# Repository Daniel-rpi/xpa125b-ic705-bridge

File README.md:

# IC-705 ↔ Xiegu XPA125B via TTGO Bluetooth-Bridge

Ein LilyGO **TTGO T-Display v1.1** (ESP32) verbindet sich per **Bluetooth
Classic (CI-V-over-SPP)** mit einem Icom **IC-705** und steuert darüber eine
nachgeschaltete Xiegu **XPA125B**-Endstufe (100 W HF-Verstärker) vollautomatisch:
Bandumschaltung, PTT und – seit Kurzem – eine softwareseitige ALC-basierte
Schutzschaltung, die eingreift, bevor die PA in ihre eigene harte
Fehlerabschaltung läuft.

Kein Kabelsalat zwischen 705 und PA, kein manuelles Bandwechseln an der PA, und
eine grobe, aber wirksame Warnstufe vor Übersteuerung – bei einem Funkgerät, das
selbst gar keine passende ACC-Buchse für so eine PA hat.

*(English: An ESP32 board bridges an Icom IC-705 (Bluetooth CI-V) to a Xiegu
XPA125B HF amplifier — automatic band switching, PTT, and a software ALC-based
overdrive protection layer. See [docs/alc-protection.md](docs/alc-protection.md)
for a full English write-up of the protection logic.)*

## ⚠️ Sicherheitshinweise (bitte vor dem Nachbau lesen)

- **≥ 3,2 V am PTT-Eingang der XPA125B zerstört deren internen Prozessor
  dauerhaft** (laut offiziellem Handbuch). Der PTT-Ausgang des TTGO läuft daher
  ausschließlich über eine galvanische Trennung (Optokoppler bzw. MOSFET-gegen-GND,
  siehe unten) – niemals GPIO26 direkt an die PA anschließen.
- Diese Firmware sendet zur reinen Anzeige (Frequenz/Modus/TX-Status/Uhrzeit)
  **ausschließlich CI-V-Lesebefehle**. Echte Sende-Kommandos (Leistung setzen,
  Modus setzen, PTT) gibt es nur in der Tune-Sequenz (Taster) und der
  ALC-Schutzfunktion – beide sind im Quellcode ausführlich kommentiert.
- Alle hier beschriebenen Werte (Bandspannungen, PTT-Pegel, ALC-Schwellen) sind
  **an einem konkreten IC-705 und einer konkreten XPA125B gemessen**. Vor dem
  Anschließen an eigene Hardware selbst nachmessen, nicht blind übernehmen.
- Kein Ersatz für die Schutzabschaltung der PA selbst – nur eine zusätzliche,
  frühere Warnstufe.
- Nachbau/Nutzung auf eigene Verantwortung.

## Basiert auf / Danke an

Dieses Projekt wäre ohne die Vorarbeit von **DL1BZ** nicht in dieser Form
entstanden:

- [dl1bz/ESP32-IC705BT-PA](https://github.com/dl1bz/ESP32-IC705BT-PA) – das
  ursprüngliche Konzept (ESP32 + Bluetooth-CI-V + Optokoppler-PTT + PWM/RC-Band-
  spannung für eine XPA125B), inklusive Forks von
  [PE1OFO](https://github.com/PE1OFO/IC-705-BlueTooth-Controller) und
  [DK8HC](https://github.com/dk8hc/IC-705-BlueTooth-Controller).

**Wichtig, damit klar ist, was wovon abstammt:** Die hier veröffentlichte
Firmware ist ein **komplett eigenständig geschriebener Sketch** (kein Codeauszug
aus den obigen Repos, keine `CIVmasterLib`-Abhängigkeit) – die Übernahme betrifft
das **Konzept und einzelne kalibrierte Werte**: die Verdrahtung
GPIO26→PTT/GPIO27→Bandspannung, die Bandspannungstabelle aus dem Xiegu-Handbuch
und die daraus abgeleitete Lastkorrektur (`corrMv` in `firmware/bands.h`) sind
1:1 aus `z_userprog.ino` von DL1BZ übernommen. Alles Weitere (TFT-Anzeige,
Uhrzeit/UTC, Tune-Sequenz mit FB/NG-Bestätigung, ALC-Auslesung samt
Schutzschaltung, das komplette PMR-171-BLE-Modul, die Daughterboard-Platine) ist
eigene Arbeit dieses Projekts.

## Fotos

| Rückseite (fertiges Modul) | Draufsicht (fertiges Modul) | Innenansicht |
|---|---|---|
|  |  |  |

## Hardware

### Übersicht

```
IC-705 ──(Bluetooth Classic, CI-V-over-SPP)──> TTGO T-Display v1.1 (ESP32)
                                                     │  GPIO26 (PTT, über Opto/MOSFET gegen GND)
                                                     │  GPIO27 (PWM → RC 470Ω/22µF → Bandspannung)
                                                     │  GPIO36 (ADC, über 220Ω ← ALC-Ausgang, Pin 4)
                                                     ▼
                                        Xiegu XPA125B – ACC-Buchse (6-pol. Mini-DIN)
                                        Pin 1 = +12…14,5V (Versorgung der Platine) ⚠️ siehe unten
                                        Pin 2 = PTT (≥3,2V = Prozessorschaden!)
                                        Pin 3 = Bandspannung
                                        Pin 4 = ALC-Ausgang (~1–4V, invertiert)
                                        Pin 6 = GND
```

> **⚠️ ACC-Pin 1 ist im offiziellen Xiegu-Handbuch als N/C (nicht belegt)
> dokumentiert – liegt bei unserem (unmodifizierten, werksseitigen) Exemplar
> aber real die volle Versorgungsspannung der PA an** (gemessen ~12,85 V bei
> eingeschalteter PA am Netzteil, skaliert entsprechend mit der extern
> angelegten 12–14,5 V-Spannung). Genau das macht die eigene Stromversorgung
> des TTGO über die ACC-Buchse erst möglich, ohne ein zweites Netzteil oder
> einen Eingriff in die PA. Diese Diskrepanz zwischen Handbuch und Realität hat
> uns selbst lange beschäftigt (mehrere Diskussionsrunden, bis wir es am Ende
> direkt mit dem Multimeter durchgemessen haben) – **vor dem Nachbau unbedingt
> selbst am eigenen Gerät nachmessen**, statt sich auf das Handbuch *oder*
> diese Notiz zu verlassen. Xiegu könnte diese Pinbelegung in einer anderen
> Fertigungscharge/Hardwarerevision jederzeit ändern, ohne das zu
> dokumentieren – schließlich war sie nie offiziell zugesichert.

Das TTGO bezieht seine eigene 3,3-V-Versorgung direkt aus dieser
(inoffiziellen, aber real anliegenden) ACC-Pin-1-Spannung der PA (isolierter
DC/DC-Wandler bzw. Buck-Regler auf dem Daughterboard, siehe `hardware/`) –
**kein separates USB-Netzteil nötig, aber USB und PA-Strom dürfen nicht
gleichzeitig anliegen** (kein Akku auf der Platine, zwei Spannungsquellen
würden sich gegenseitig stören).

### Eigene SMD-Platine (Daughterboard)

Statt der Verkabelung frei fliegend aufzubauen: ein fertig geroutetes,
2-lagiges Daughterboard, das exakt auf die Stiftleisten des TTGO T-Display v1.1
gesteckt wird (Pin-Raster 1:1 aus der offiziellen LilyGO-Eagle-Bibliothek
übernommen), inkl. isoliertem Step-Down-Wandler, PTT-Schaltung und
RC-Filter für die Bandspannung.

- **[hardware/DESIGN.md](hardware/DESIGN.md)** – vollständige Bauteilliste,
  Netzliste, Layout-Vorgaben, Inbetriebnahme-Checkliste
- **[hardware/BESTELLUNG.md](hardware/BESTELLUNG.md)** – Schritt-für-Schritt
  JLCPCB-Bestellanleitung
- **`hardware/kicad/`** – fertig geroutetes KiCad-Projekt (DRC-geprüft)
- **`hardware/gerber/`** – Gerber + BOM + CPL, fertig für den JLCPCB-Upload
- **`images/`** – Renderansichten sowie reale Fotos des bestückten Boards

Die im finalen PCB-Entwurf verwendete PTT-Schaltung (N-MOSFET gegen GND) ist
eine bewusste, im Prototyp **nicht** getestete Vereinfachung gegenüber dem
ursprünglich verifizierten Optokoppler-Aufbau – Details und Begründung in
`hardware/DESIGN.md`. Der Optokoppler-Aufbau selbst ist am realen Gerät
vollständig getestet (siehe unten).

## Firmware

`firmware/ttgo_xpa_bridge.ino` (+ `bands.h`, `tft_setup.h`) – ein einziger
Arduino-Sketch für das TTGO T-Display v1.1 (Board-Definition:
`esp32:esp32:lilygo_t_display`, Arduino-ESP32-Core 3.x).

### Funktionen

- **Live-Anzeige** auf dem eingebauten TFT: Frequenz, Modulationsart, Band,
  RX/TX-Status, Uhrzeit (lokal + UTC, aus dem 705 ausgelesen), S-Meter.
- **Automatische Bandumschaltung** der XPA125B passend zur 705-Frequenz (PWM →
  RC-Tiefpass → Bandspannung, Tabelle inkl. Lastkorrektur in `bands.h`).
- **PTT-Durchschaltung** – der 705 meldet TX per CI-V-Broadcast/FastPTT-Push,
  das TTGO schaltet die PA-PTT-Leitung synchron mit.
- **Tune-Taster** (oberer Button, Mehrfachklick = längere Haltezeit): setzt
  kurzzeitig Leistung + Modus (FM statt CW – siehe Kommentar im Code, PTT-only
  erzeugt in CW keinen Träger), keyt den XPA125B-eigenen Antennentuner, stellt
  danach den Ausgangszustand wieder her. Jeder Schritt wartet auf eine
  FB(OK)/FA(NG)-Bestätigung; bei Fehlschlag Eskalation bis zur kompletten
  Geräteabschaltung (Cmd `18 00`).
- **ALC-Schutzschaltung** (neu, 2026-09-27) – siehe
  **[docs/alc-protection.md](docs/alc-protection.md)** für die volle
  Herleitung, Kalibrierdaten und Begründung, warum ein einfacher gleitender
  Mittelwert dafür nicht ausreicht.
- **Persistentes ALC/Leistungs-Logging** auf SPIFFS (überlebt den
  USB/PA-Stromwechsel, den ein reiner RAM-Puffer nicht überlebt hätte).
- **Zweiter Funkgeräte-Modus (PMR-171, Bluetooth LE)** – per langem Tastendruck
  umschaltbar (in NVS/`Preferences` persistiert). Eigenständiges Protokoll
  (BLE GATT statt Classic SPP), teilt sich aber Anzeige/GPIO-Grundgerüst mit dem
  705-Modus. Die ALC-Schutzschaltung ist **bewusst 705-spezifisch** und bleibt
  in diesem Modus inaktiv.
- **Automatischer Bluetooth-Reconnect**: das Board ist gleichzeitig
  BT-Server (nimmt Verbindungen vom 705 an) und -Master (verbindet sich aktiv
  zu bereits gekoppelten Geräten) – deckt sowohl "705 verbindet sich selbst"
  als auch "705 hat die Verbindung verloren, TTGO holt sie aktiv zurück" ab.

### Serial-Kommandos (USB, 115200 Baud, nur wenn USB angeschlossen – siehe
Sicherheitshinweis oben zur PA-Stromversorgung)

| Kommando | Wirkung |
|---|---|
| `dbg on` / `dbg off` | rohe CI-V-Frames auf der Konsole mitloggen |
| `fastptt on` | fastPTT-Push (`24 00 00 01`) aktivieren |
| `txpoll <ms>` | Poll-Intervall für den TX-Status |
| `band <name\|zero\|auto>` | Bandspannung manuell fixieren/automatisch |
| `alclog dump` / `clear` / `status` | ALC/Leistungs-Log (SPIFFS) auslesen/löschen/Status |
| `alcprotect on` / `off` | Schutzschaltung ohne Neuflashen de-/aktivieren |

### Flashen

```bash
arduino-cli core install esp32:esp32
arduino-cli compile --fqbn esp32:esp32:lilygo_t_display firmware/ttgo_xpa_bridge.ino
arduino-cli upload -p /dev/ttyXXX --fqbn esp32:esp32:lilygo_t_display firmware/ttgo_xpa_bridge.ino
```

Getestet mit Arduino-ESP32-Core 3.3.11.

## Status

- **Optokoppler-Prototyp (frei verdrahtet):** live an der echten XPA125B
  verifiziert – Bandumschaltung, PTT, Tune-Sequenz, ALC-Auslesung und die
  Schutzschaltung wurden alle mit echter Hardware getestet.
- **SMD-Daughterboard (MOSFET-Variante):** gefertigt, bestückt und am realen
  Gerät montiert (siehe Fotos oben) – zeigt live Frequenz/Modus/RX-Status vom
  705. Die PTT-Schaltung dieser Variante ist damit im Aufbau bestätigt; ein
  vollständiger, ausführlicher Sende-Test steht als Nächstes an (siehe
  `hardware/DESIGN.md`).
- **ALC-Schutzschaltung:** live getestet in FM (Kollapspunkt sauber erkannt)
  und SSB (vierstufige automatische Rückregelungs-Kaskade beobachtet, hat einen
  drohenden PA-Fehlerabschaltung erfolgreich verhindert).

## Lizenz

Eigener Code (Firmware, PCB-Design) unter [MIT-Lizenz](LICENSE). Die in
`firmware/bands.h` übernommene Bandspannungs-/Lastkorrekturtabelle stammt aus
DL1BZs `z_userprog.ino` (siehe Danke-Abschnitt) – bitte bei Weiterverwendung
dieser konkreten Werte entsprechend referenzieren.

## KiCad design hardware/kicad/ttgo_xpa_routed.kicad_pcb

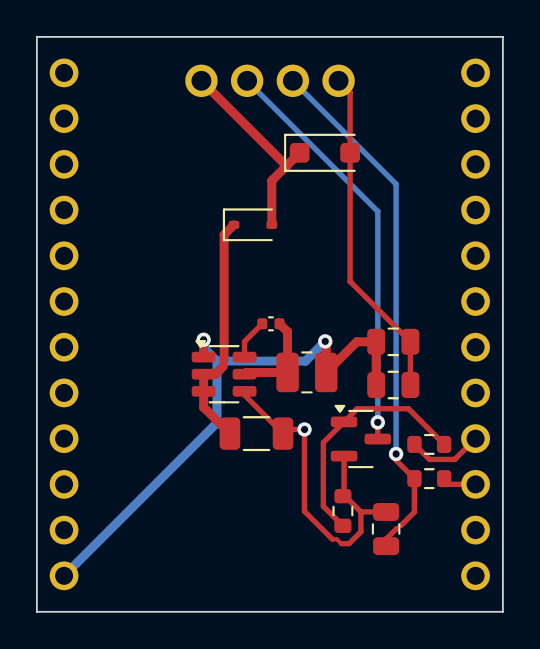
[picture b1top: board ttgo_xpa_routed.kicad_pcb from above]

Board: 2 copper layers, 25.9 x 31.9 mm, 15 parts (0 on the bottom side), 11 nets.

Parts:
C1: 10uF/50V; C_1206_3216Metric
C2, C3, C5: 22uF/25V; C_0805_2012Metric
C4: 100nF; C_0402_1005Metric
D1: 1N5819WS; D_SOD-323
D2: SMF18CA; D_SOD-123F
J1: ACC-Kabel
J2: TTGO-Header-24
L1: 4.7uH; L_1008_2520Metric
Q1: AO3400A; SOT-23
R1: 470R; R_0603_1608Metric
R2: 100R; R_0603_1608Metric
R3: 100k; R_0603_1608Metric
U1: AP63203WU-7; TSOT-23-6

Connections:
3V3: C2.1, C3.1, J2.L1, L1.2, U1.1
+12V: C1.1, D1.1, U1.2, U1.3
+12V_RAW: D1.2, D2.1, J1.1
BAND: C5.1, J1.3, R1.1
BST: C4.1, U1.6
G26: J2.R4, R2.1
G27: J2.R3, R1.2
GATE: Q1.1, R2.2, R3.1
GND: C1.2, C2.2, C3.2, C5.2, D2.2, J1.4, J2.R2, Q1.2, R3.2, U1.4
PTT: J1.2, Q1.3
SW: C4.2, L1.1, U1.5
